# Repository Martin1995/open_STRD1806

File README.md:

# open_STRD1806

Open hardware reconstruction of the Sanken STR-D1806 hybrid IC for SMPS (Switch Mode Power Supplies).

## 🚨 Disclaimer & Safety Warning
* **Status:** This design is **untested** (Alpha), but mostly follows the original circuit design of the STR-D1806.
* **Warranty:** The schematic, PCB design, and manufacturing files are provided **"as is" without any warranty or guarantee of function**.
* **Risk:** High voltage is dangerous. The use, building, and testing of this design is entirely **at your own risk**. 

## ⚡ Technical Specification
The circuit board is designed to work in switch-mode power supplies with input voltages up to **240V AC RMS** (rectified to approximately **340V DC** on the primary rail). 

The PCB is designed as a single-sided board, optimized for **Aluminum Substrate / IMS (Insulated Metal Substrate) manufacturing** to ensure optimal thermal dissipation to the original heatsink of the PSU.
The PCB accepts either **D2PAK(TO-263)** or **TO-220** packages for the surface mounted **Power NPN Transistor**

## License
The files are provided under the following license:
**CERN-OHL-S**

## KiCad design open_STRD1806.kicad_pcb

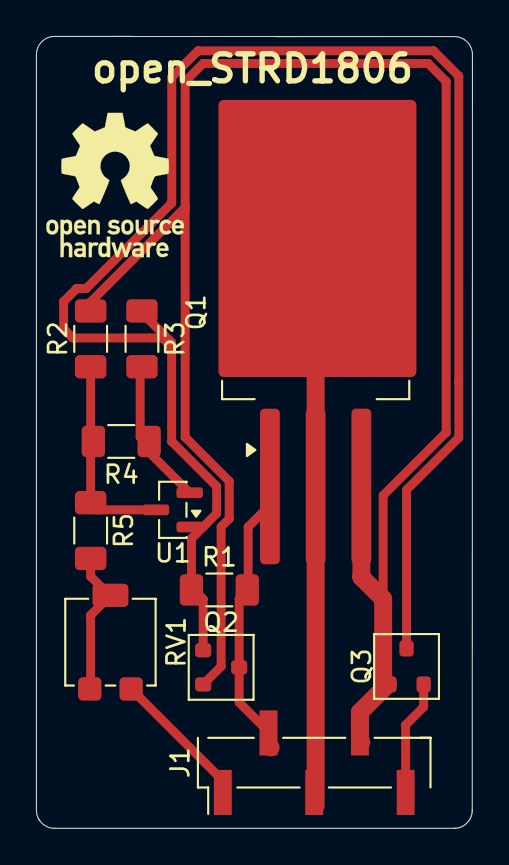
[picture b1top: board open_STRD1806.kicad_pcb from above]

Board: 2 copper layers, 24.2 x 44.0 mm, 11 parts (0 on the bottom side), 9 nets.

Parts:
J1: Conn_01x05; PinHeader_1x05_P2.54mm_Vertical_SMD_Pin1Left
Q1: NPN; TO-263-3_+TO-220_Combo_TabPin2
Q2: BC857; SOT-23
Q3: BC847; SOT-23
R1, R2, R3, R4: R; R_1206_3216Metric_Pad1.30x1.75mm_HandSolder
R5: 1K; R_1206_3216Metric_Pad1.30x1.75mm_HandSolder
RV1: R_Potentiometer; Potentiometer_Bourns_3224G_Horizontal
U1: TL431DBZ; SOT-23

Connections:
/FB: J1.1, RV1.1
/Power_B: J1.2, Q1.1 (B), Q2.3 (C), R1.2
/Power_C: J1.3, Q1.2 (C)
/Power_E: J1.4, Q1.3 (E), Q2.2 (E), Q3.1 (B), R2.2
/Shunt_E: J1.5, Q3.2 (E)
unnamed: Q2.1 (B), Q3.3 (C), R1.1, R3.1, U1.1 (K)
unnamed: R5.2, RV1.2, RV1.3
unnamed: R2.1, R4.2, R5.1, U1.3 (A)
unnamed: R3.2, R4.1, U1.2 (REF)
